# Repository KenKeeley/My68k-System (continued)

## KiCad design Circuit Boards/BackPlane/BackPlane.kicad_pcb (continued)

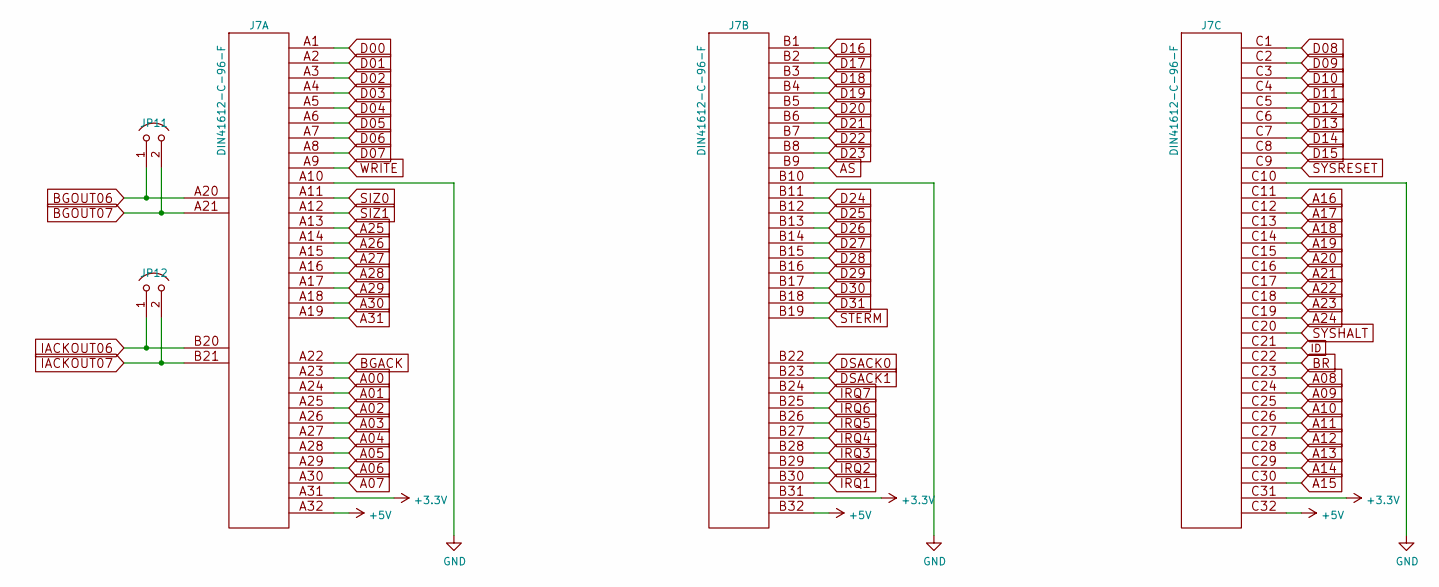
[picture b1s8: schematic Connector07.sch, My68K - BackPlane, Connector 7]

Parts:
J7: DIN41612-C-96-F; Part No. 1656359
JP11, JP12: Jumper; Part No. 1593411

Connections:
+3V3: J7.A31, J7.B31, J7.C31; also elsewhere on the board
+5V: J7.A32, J7.B32, J7.C32; also elsewhere on the board
A00: J7.A23; also elsewhere on the board
A01: J7.A24; also elsewhere on the board
A02: J7.A25; also elsewhere on the board
A03: J7.A26; also elsewhere on the board
A04: J7.A27; also elsewhere on the board
A05: J7.A28; also elsewhere on the board
A06: J7.A29; also elsewhere on the board
A07: J7.A30; also elsewhere on the board
A08: J7.C23; also elsewhere on the board
A09: J7.C24; also elsewhere on the board
A10: J7.C25; also elsewhere on the board
A11: J7.C26; also elsewhere on the board
A12: J7.C27; also elsewhere on the board
A13: J7.C28; also elsewhere on the board
A14: J7.C29; also elsewhere on the board
A15: J7.C30; also elsewhere on the board
A16: J7.C11; also elsewhere on the board
A17: J7.C12; also elsewhere on the board
A18: J7.C13; also elsewhere on the board
A19: J7.C14; also elsewhere on the board
A20: J7.C15; also elsewhere on the board
A21: J7.C16; also elsewhere on the board
A22: J7.C17; also elsewhere on the board
A23: J7.C18; also elsewhere on the board
A24: J7.C19; also elsewhere on the board
A25: J7.A13; also elsewhere on the board
A26: J7.A14; also elsewhere on the board
A27: J7.A15; also elsewhere on the board
A28: J7.A16; also elsewhere on the board
A29: J7.A17; also elsewhere on the board
A30: J7.A18; also elsewhere on the board
A31: J7.A19; also elsewhere on the board
AS: J7.B9; also elsewhere on the board
BGACK: J7.A22; also elsewhere on the board
BGOUT06: J7.A20, JP11.1; also elsewhere on the board
BGOUT07: J7.A21, JP11.2; also elsewhere on the board
BR: J7.C22; also elsewhere on the board
D00: J7.A1; also elsewhere on the board
D01: J7.A2; also elsewhere on the board
D02: J7.A3; also elsewhere on the board
D03: J7.A4; also elsewhere on the board
D04: J7.A5; also elsewhere on the board
D05: J7.A6; also elsewhere on the board
D06: J7.A7; also elsewhere on the board
D07: J7.A8; also elsewhere on the board
D08: J7.C1; also elsewhere on the board
D09: J7.C2; also elsewhere on the board
D10: J7.C3; also elsewhere on the board
D11: J7.C4; also elsewhere on the board
D12: J7.C5; also elsewhere on the board
D13: J7.C6; also elsewhere on the board
D14: J7.C7; also elsewhere on the board
D15: J7.C8; also elsewhere on the board
D16: J7.B1; also elsewhere on the board
D17: J7.B2; also elsewhere on the board
D18: J7.B3; also elsewhere on the board
D19: J7.B4; also elsewhere on the board
D20: J7.B5; also elsewhere on the board
D21: J7.B6; also elsewhere on the board
D22: J7.B7; also elsewhere on the board
D23: J7.B8; also elsewhere on the board
D24: J7.B11; also elsewhere on the board
D25: J7.B12; also elsewhere on the board
D26: J7.B13; also elsewhere on the board
D27: J7.B14; also elsewhere on the board
D28: J7.B15; also elsewhere on the board
D29: J7.B16; also elsewhere on the board
D30: J7.B17; also elsewhere on the board
D31: J7.B18; also elsewhere on the board
DSACK0: J7.B22; also elsewhere on the board
DSACK1: J7.B23; also elsewhere on the board
GND: J7.33 (GND), J7.34 (GND), J7.A10, J7.B10, J7.C10; also elsewhere on the board
IACKOUT06: J7.B20, JP12.1; also elsewhere on the board
IACKOUT07: J7.B21, JP12.2; also elsewhere on the board
ID: J7.C21; also elsewhere on the board
IRQ1: J7.B30; also elsewhere on the board
IRQ2: J7.B29; also elsewhere on the board
IRQ3: J7.B28; also elsewhere on the board
IRQ4: J7.B27; also elsewhere on the board
IRQ5: J7.B26; also elsewhere on the board
IRQ6: J7.B25; also elsewhere on the board
IRQ7: J7.B24; also elsewhere on the board
SIZ0: J7.A11; also elsewhere on the board
SIZ1: J7.A12; also elsewhere on the board
STERM: J7.B19; also elsewhere on the board
SYSHALT: J7.C20; also elsewhere on the board
SYSRESET: J7.C9; also elsewhere on the board
WRITE: J7.A9; also elsewhere on the board

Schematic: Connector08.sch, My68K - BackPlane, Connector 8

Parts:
J8: DIN41612-C-96-F; Part No. 1656359
JP13, JP14: Jumper; Part No. 1593411

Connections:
+3V3: J8.A31, J8.B31, J8.C31; also elsewhere on the board
+5V: J8.A32, J8.B32, J8.C32; also elsewhere on the board
A00: J8.A23; also elsewhere on the board
A01: J8.A24; also elsewhere on the board
A02: J8.A25; also elsewhere on the board
A03: J8.A26; also elsewhere on the board
A04: J8.A27; also elsewhere on the board
A05: J8.A28; also elsewhere on the board
A06: J8.A29; also elsewhere on the board
A07: J8.A30; also elsewhere on the board
A08: J8.C23; also elsewhere on the board
A09: J8.C24; also elsewhere on the board
A10: J8.C25; also elsewhere on the board
A11: J8.C26; also elsewhere on the board
A12: J8.C27; also elsewhere on the board
A13: J8.C28; also elsewhere on the board
A14: J8.C29; also elsewhere on the board
A15: J8.C30; also elsewhere on the board
A16: J8.C11; also elsewhere on the board
A17: J8.C12; also elsewhere on the board
A18: J8.C13; also elsewhere on the board
A19: J8.C14; also elsewhere on the board
A20: J8.C15; also elsewhere on the board
A21: J8.C16; also elsewhere on the board
A22: J8.C17; also elsewhere on the board
A23: J8.C18; also elsewhere on the board
A24: J8.C19; also elsewhere on the board
A25: J8.A13; also elsewhere on the board
A26: J8.A14; also elsewhere on the board
A27: J8.A15; also elsewhere on the board
A28: J8.A16; also elsewhere on the board
A29: J8.A17; also elsewhere on the board
A30: J8.A18; also elsewhere on the board
A31: J8.A19; also elsewhere on the board
AS: J8.B9; also elsewhere on the board
BGACK: J8.A22; also elsewhere on the board
BGOUT07: J8.A20, JP13.1; also elsewhere on the board
BGOUT08: J8.A21, JP13.2; also elsewhere on the board
BR: J8.C22; also elsewhere on the board
D00: J8.A1; also elsewhere on the board
D01: J8.A2; also elsewhere on the board
D02: J8.A3; also elsewhere on the board
D03: J8.A4; also elsewhere on the board
D04: J8.A5; also elsewhere on the board
D05: J8.A6; also elsewhere on the board
D06: J8.A7; also elsewhere on the board
D07: J8.A8; also elsewhere on the board
D08: J8.C1; also elsewhere on the board
D09: J8.C2; also elsewhere on the board
D10: J8.C3; also elsewhere on the board
D11: J8.C4; also elsewhere on the board
D12: J8.C5; also elsewhere on the board
D13: J8.C6; also elsewhere on the board
D14: J8.C7; also elsewhere on the board
D15: J8.C8; also elsewhere on the board
D16: J8.B1; also elsewhere on the board
D17: J8.B2; also elsewhere on the board
D18: J8.B3; also elsewhere on the board
D19: J8.B4; also elsewhere on the board
D20: J8.B5; also elsewhere on the board
D21: J8.B6; also elsewhere on the board
D22: J8.B7; also elsewhere on the board
D23: J8.B8; also elsewhere on the board
D24: J8.B11; also elsewhere on the board
D25: J8.B12; also elsewhere on the board
D26: J8.B13; also elsewhere on the board
D27: J8.B14; also elsewhere on the board
D28: J8.B15; also elsewhere on the board
D29: J8.B16; also elsewhere on the board
D30: J8.B17; also elsewhere on the board
D31: J8.B18; also elsewhere on the board
DSACK0: J8.B22; also elsewhere on the board
DSACK1: J8.B23; also elsewhere on the board
GND: J8.33 (GND), J8.34 (GND), J8.A10, J8.B10, J8.C10; also elsewhere on the board
IACKOUT07: J8.B20, JP14.1; also elsewhere on the board
IACKOUT08: J8.B21, JP14.2; also elsewhere on the board
ID: J8.C21; also elsewhere on the board
IRQ1: J8.B30; also elsewhere on the board
IRQ2: J8.B29; also elsewhere on the board
IRQ3: J8.B28; also elsewhere on the board
IRQ4: J8.B27; also elsewhere on the board
IRQ5: J8.B26; also elsewhere on the board
IRQ6: J8.B25; also elsewhere on the board
IRQ7: J8.B24; also elsewhere on the board
SIZ0: J8.A11; also elsewhere on the board
SIZ1: J8.A12; also elsewhere on the board
STERM: J8.B19; also elsewhere on the board
SYSHALT: J8.C20; also elsewhere on the board
SYSRESET: J8.C9; also elsewhere on the board
WRITE: J8.A9; also elsewhere on the board

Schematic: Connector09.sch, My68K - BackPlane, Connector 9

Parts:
J9: DIN41612-C-96-F; Part No. 1656359
JP15, JP16: Jumper; Part No. 1593411

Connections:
+3V3: J9.A31, J9.B31, J9.C31; also elsewhere on the board
+5V: J9.A32, J9.B32, J9.C32; also elsewhere on the board
A00: J9.A23; also elsewhere on the board
A01: J9.A24; also elsewhere on the board
A02: J9.A25; also elsewhere on the board
A03: J9.A26; also elsewhere on the board
A04: J9.A27; also elsewhere on the board
A05: J9.A28; also elsewhere on the board
A06: J9.A29; also elsewhere on the board
A07: J9.A30; also elsewhere on the board
A08: J9.C23; also elsewhere on the board
A09: J9.C24; also elsewhere on the board
A10: J9.C25; also elsewhere on the board
A11: J9.C26; also elsewhere on the board
A12: J9.C27; also elsewhere on the board
A13: J9.C28; also elsewhere on the board
A14: J9.C29; also elsewhere on the board
A15: J9.C30; also elsewhere on the board
A16: J9.C11; also elsewhere on the board
A17: J9.C12; also elsewhere on the board
A18: J9.C13; also elsewhere on the board
A19: J9.C14; also elsewhere on the board
A20: J9.C15; also elsewhere on the board
A21: J9.C16; also elsewhere on the board
A22: J9.C17; also elsewhere on the board
A23: J9.C18; also elsewhere on the board
A24: J9.C19; also elsewhere on the board
A25: J9.A13; also elsewhere on the board
A26: J9.A14; also elsewhere on the board
A27: J9.A15; also elsewhere on the board
A28: J9.A16; also elsewhere on the board
A29: J9.A17; also elsewhere on the board
A30: J9.A18; also elsewhere on the board
A31: J9.A19; also elsewhere on the board
AS: J9.B9; also elsewhere on the board
BGACK: J9.A22; also elsewhere on the board
BGOUT08: J9.A20, JP15.1; also elsewhere on the board
BGOUT09: J9.A21, JP15.2; also elsewhere on the board
BR: J9.C22; also elsewhere on the board
D00: J9.A1; also elsewhere on the board
D01: J9.A2; also elsewhere on the board
D02: J9.A3; also elsewhere on the board
D03: J9.A4; also elsewhere on the board
D04: J9.A5; also elsewhere on the board
D05: J9.A6; also elsewhere on the board
D06: J9.A7; also elsewhere on the board
D07: J9.A8; also elsewhere on the board
D08: J9.C1; also elsewhere on the board
D09: J9.C2; also elsewhere on the board
D10: J9.C3; also elsewhere on the board
D11: J9.C4; also elsewhere on the board
D12: J9.C5; also elsewhere on the board
D13: J9.C6; also elsewhere on the board
D14: J9.C7; also elsewhere on the board
D15: J9.C8; also elsewhere on the board
D16: J9.B1; also elsewhere on the board
D17: J9.B2; also elsewhere on the board
D18: J9.B3; also elsewhere on the board
D19: J9.B4; also elsewhere on the board
D20: J9.B5; also elsewhere on the board
D21: J9.B6; also elsewhere on the board
D22: J9.B7; also elsewhere on the board
D23: J9.B8; also elsewhere on the board
D24: J9.B11; also elsewhere on the board
D25: J9.B12; also elsewhere on the board
D26: J9.B13; also elsewhere on the board
D27: J9.B14; also elsewhere on the board
D28: J9.B15; also elsewhere on the board
D29: J9.B16; also elsewhere on the board
D30: J9.B17; also elsewhere on the board
D31: J9.B18; also elsewhere on the board
DSACK0: J9.B22; also elsewhere on the board
DSACK1: J9.B23; also elsewhere on the board
GND: J9.33 (GND), J9.34 (GND), J9.A10, J9.B10, J9.C10; also elsewhere on the board
IACKOUT08: J9.B20, JP16.1; also elsewhere on the board
IACKOUT09: J9.B21, JP16.2; also elsewhere on the board
ID: J9.C21; also elsewhere on the board
IRQ1: J9.B30; also elsewhere on the board
IRQ2: J9.B29; also elsewhere on the board
IRQ3: J9.B28; also elsewhere on the board
IRQ4: J9.B27; also elsewhere on the board
IRQ5: J9.B26; also elsewhere on the board
IRQ6: J9.B25; also elsewhere on the board
IRQ7: J9.B24; also elsewhere on the board
SIZ0: J9.A11; also elsewhere on the board
SIZ1: J9.A12; also elsewhere on the board
STERM: J9.B19; also elsewhere on the board
SYSHALT: J9.C20; also elsewhere on the board
SYSRESET: J9.C9; also elsewhere on the board
WRITE: J9.A9; also elsewhere on the board

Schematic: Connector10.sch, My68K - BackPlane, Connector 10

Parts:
J10: DIN41612-C-96-F; Part No. 1656359
JP17, JP18: Jumper; Part No. 1593411

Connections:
+3V3: J10.A31, J10.B31, J10.C31; also elsewhere on the board
+5V: J10.A32, J10.B32, J10.C32; also elsewhere on the board
A00: J10.A23; also elsewhere on the board
A01: J10.A24; also elsewhere on the board
A02: J10.A25; also elsewhere on the board
A03: J10.A26; also elsewhere on the board
A04: J10.A27; also elsewhere on the board
A05: J10.A28; also elsewhere on the board
A06: J10.A29; also elsewhere on the board
A07: J10.A30; also elsewhere on the board
A08: J10.C23; also elsewhere on the board
A09: J10.C24; also elsewhere on the board
A10: J10.C25; also elsewhere on the board
A11: J10.C26; also elsewhere on the board
A12: J10.C27; also elsewhere on the board
A13: J10.C28; also elsewhere on the board
A14: J10.C29; also elsewhere on the board
A15: J10.C30; also elsewhere on the board
A16: J10.C11; also elsewhere on the board
A17: J10.C12; also elsewhere on the board
A18: J10.C13; also elsewhere on the board
A19: J10.C14; also elsewhere on the board
A20: J10.C15; also elsewhere on the board
A21: J10.C16; also elsewhere on the board
A22: J10.C17; also elsewhere on the board
A23: J10.C18; also elsewhere on the board
A24: J10.C19; also elsewhere on the board
A25: J10.A13; also elsewhere on the board
A26: J10.A14; also elsewhere on the board
A27: J10.A15; also elsewhere on the board
A28: J10.A16; also elsewhere on the board
A29: J10.A17; also elsewhere on the board
A30: J10.A18; also elsewhere on the board
A31: J10.A19; also elsewhere on the board
AS: J10.B9; also elsewhere on the board
BGACK: J10.A22; also elsewhere on the board
BGOUT09: J10.A20, JP17.1; also elsewhere on the board
BGOUT10: J10.A21, JP17.2; also elsewhere on the board
BR: J10.C22; also elsewhere on the board
D00: J10.A1; also elsewhere on the board
D01: J10.A2; also elsewhere on the board
D02: J10.A3; also elsewhere on the board
D03: J10.A4; also elsewhere on the board
D04: J10.A5; also elsewhere on the board
D05: J10.A6; also elsewhere on the board
D06: J10.A7; also elsewhere on the board
D07: J10.A8; also elsewhere on the board
D08: J10.C1; also elsewhere on the board
D09: J10.C2; also elsewhere on the board
D10: J10.C3; also elsewhere on the board
D11: J10.C4; also elsewhere on the board
D12: J10.C5; also elsewhere on the board
D13: J10.C6; also elsewhere on the board
D14: J10.C7; also elsewhere on the board
D15: J10.C8; also elsewhere on the board
D16: J10.B1; also elsewhere on the board
D17: J10.B2; also elsewhere on the board
D18: J10.B3; also elsewhere on the board
D19: J10.B4; also elsewhere on the board
D20: J10.B5; also elsewhere on the board
D21: J10.B6; also elsewhere on the board
D22: J10.B7; also elsewhere on the board
D23: J10.B8; also elsewhere on the board
D24: J10.B11; also elsewhere on the board
D25: J10.B12; also elsewhere on the board
D26: J10.B13; also elsewhere on the board
D27: J10.B14; also elsewhere on the board
D28: J10.B15; also elsewhere on the board
D29: J10.B16; also elsewhere on the board
D30: J10.B17; also elsewhere on the board
D31: J10.B18; also elsewhere on the board
DSACK0: J10.B22; also elsewhere on the board
DSACK1: J10.B23; also elsewhere on the board
GND: J10.33 (GND), J10.34 (GND), J10.A10, J10.B10, J10.C10; also elsewhere on the board
IACKOUT09: J10.B20, JP18.1; also elsewhere on the board
IACKOUT10: J10.B21, JP18.2; also elsewhere on the board
ID: J10.C21; also elsewhere on the board
IRQ1: J10.B30; also elsewhere on the board
IRQ2: J10.B29; also elsewhere on the board
IRQ3: J10.B28; also elsewhere on the board
IRQ4: J10.B27; also elsewhere on the board
IRQ5: J10.B26; also elsewhere on the board
IRQ6: J10.B25; also elsewhere on the board
IRQ7: J10.B24; also elsewhere on the board
SIZ0: J10.A11; also elsewhere on the board
SIZ1: J10.A12; also elsewhere on the board
STERM: J10.B19; also elsewhere on the board
SYSHALT: J10.C20; also elsewhere on the board
SYSRESET: J10.C9; also elsewhere on the board
WRITE: J10.A9; also elsewhere on the board

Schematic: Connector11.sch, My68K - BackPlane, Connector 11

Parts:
J11: DIN41612-C-96-F; Part No. 1656359
JP19, JP20: Jumper; Part No. 1593411

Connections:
+3V3: J11.A31, J11.B31, J11.C31; also elsewhere on the board
+5V: J11.A32, J11.B32, J11.C32; also elsewhere on the board
A00: J11.A23; also elsewhere on the board
A01: J11.A24; also elsewhere on the board
A02: J11.A25; also elsewhere on the board
A03: J11.A26; also elsewhere on the board
A04: J11.A27; also elsewhere on the board
A05: J11.A28; also elsewhere on the board
A06: J11.A29; also elsewhere on the board
A07: J11.A30; also elsewhere on the board
A08: J11.C23; also elsewhere on the board
A09: J11.C24; also elsewhere on the board
A10: J11.C25; also elsewhere on the board
A11: J11.C26; also elsewhere on the board
A12: J11.C27; also elsewhere on the board
A13: J11.C28; also elsewhere on the board
A14: J11.C29; also elsewhere on the board
A15: J11.C30; also elsewhere on the board
A16: J11.C11; also elsewhere on the board
A17: J11.C12; also elsewhere on the board
A18: J11.C13; also elsewhere on the board
A19: J11.C14; also elsewhere on the board
A20: J11.C15; also elsewhere on the board
A21: J11.C16; also elsewhere on the board
A22: J11.C17; also elsewhere on the board
A23: J11.C18; also elsewhere on the board
A24: J11.C19; also elsewhere on the board
A25: J11.A13; also elsewhere on the board
A26: J11.A14; also elsewhere on the board
A27: J11.A15; also elsewhere on the board
A28: J11.A16; also elsewhere on the board
A29: J11.A17; also elsewhere on the board
A30: J11.A18; also elsewhere on the board
A31: J11.A19; also elsewhere on the board
AS: J11.B9; also elsewhere on the board
BGACK: J11.A22; also elsewhere on the board
BGOUT10: J11.A20, JP19.1; also elsewhere on the board
BGOUT11: J11.A21, JP19.2; also elsewhere on the board
BR: J11.C22; also elsewhere on the board
D00: J11.A1; also elsewhere on the board
D01: J11.A2; also elsewhere on the board
D02: J11.A3; also elsewhere on the board
D03: J11.A4; also elsewhere on the board
D04: J11.A5; also elsewhere on the board
D05: J11.A6; also elsewhere on the board
D06: J11.A7; also elsewhere on the board
D07: J11.A8; also elsewhere on the board
D08: J11.C1; also elsewhere on the board
D09: J11.C2; also elsewhere on the board
D10: J11.C3; also elsewhere on the board
D11: J11.C4; also elsewhere on the board
D12: J11.C5; also elsewhere on the board
D13: J11.C6; also elsewhere on the board
D14: J11.C7; also elsewhere on the board
D15: J11.C8; also elsewhere on the board
D16: J11.B1; also elsewhere on the board
D17: J11.B2; also elsewhere on the board
D18: J11.B3; also elsewhere on the board
D19: J11.B4; also elsewhere on the board
D20: J11.B5; also elsewhere on the board
D21: J11.B6; also elsewhere on the board
D22: J11.B7; also elsewhere on the board
D23: J11.B8; also elsewhere on the board
D24: J11.B11; also elsewhere on the board
D25: J11.B12; also elsewhere on the board
D26: J11.B13; also elsewhere on the board
D27: J11.B14; also elsewhere on the board
D28: J11.B15; also elsewhere on the board
D29: J11.B16; also elsewhere on the board
D30: J11.B17; also elsewhere on the board
D31: J11.B18; also elsewhere on the board
DSACK0: J11.B22; also elsewhere on the board
DSACK1: J11.B23; also elsewhere on the board
GND: J11.33 (GND), J11.34 (GND), J11.A10, J11.B10, J11.C10; also elsewhere on the board
IACKOUT10: J11.B20, JP20.1; also elsewhere on the board
IACKOUT11: J11.B21, JP20.2; also elsewhere on the board
ID: J11.C21; also elsewhere on the board
IRQ1: J11.B30; also elsewhere on the board
IRQ2: J11.B29; also elsewhere on the board
IRQ3: J11.B28; also elsewhere on the board
IRQ4: J11.B27; also elsewhere on the board
IRQ5: J11.B26; also elsewhere on the board
IRQ6: J11.B25; also elsewhere on the board
IRQ7: J11.B24; also elsewhere on the board
SIZ0: J11.A11; also elsewhere on the board
SIZ1: J11.A12; also elsewhere on the board
STERM: J11.B19; also elsewhere on the board
SYSHALT: J11.C20; also elsewhere on the board
SYSRESET: J11.C9; also elsewhere on the board
WRITE: J11.A9; also elsewhere on the board

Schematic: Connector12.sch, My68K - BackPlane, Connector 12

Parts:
J12: DIN41612-C-96-F; Part No. 1656359
JP21, JP22: Jumper; Part No. 1593411

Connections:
+3V3: J12.A31, J12.B31, J12.C31; also elsewhere on the board
+5V: J12.A32, J12.B32, J12.C32; also elsewhere on the board
A00: J12.A23; also elsewhere on the board
A01: J12.A24; also elsewhere on the board
A02: J12.A25; also elsewhere on the board
A03: J12.A26; also elsewhere on the board
A04: J12.A27; also elsewhere on the board
A05: J12.A28; also elsewhere on the board
A06: J12.A29; also elsewhere on the board
A07: J12.A30; also elsewhere on the board
A08: J12.C23; also elsewhere on the board
A09: J12.C24; also elsewhere on the board
A10: J12.C25; also elsewhere on the board
A11: J12.C26; also elsewhere on the board
A12: J12.C27; also elsewhere on the board
A13: J12.C28; also elsewhere on the board
A14: J12.C29; also elsewhere on the board
A15: J12.C30; also elsewhere on the board
A16: J12.C11; also elsewhere on the board
A17: J12.C12; also elsewhere on the board
A18: J12.C13; also elsewhere on the board
A19: J12.C14; also elsewhere on the board
A20: J12.C15; also elsewhere on the board
A21: J12.C16; also elsewhere on the board
A22: J12.C17; also elsewhere on the board
A23: J12.C18; also elsewhere on the board
A24: J12.C19; also elsewhere on the board
A25: J12.A13; also elsewhere on the board
A26: J12.A14; also elsewhere on the board
A27: J12.A15; also elsewhere on the board
A28: J12.A16; also elsewhere on the board
A29: J12.A17; also elsewhere on the board
A30: J12.A18; also elsewhere on the board
A31: J12.A19; also elsewhere on the board
AS: J12.B9; also elsewhere on the board
BGACK: J12.A22; also elsewhere on the board
BGOUT11: J12.A20, JP21.1; also elsewhere on the board
BGOUT12: J12.A21, JP21.2; also elsewhere on the board
BR: J12.C22; also elsewhere on the board
D00: J12.A1; also elsewhere on the board
D01: J12.A2; also elsewhere on the board
D02: J12.A3; also elsewhere on the board
D03: J12.A4; also elsewhere on the board
D04: J12.A5; also elsewhere on the board
D05: J12.A6; also elsewhere on the board
D06: J12.A7; also elsewhere on the board
D07: J12.A8; also elsewhere on the board
D08: J12.C1; also elsewhere on the board
D09: J12.C2; also elsewhere on the board
D10: J12.C3; also elsewhere on the board
D11: J12.C4; also elsewhere on the board
D12: J12.C5; also elsewhere on the board
D13: J12.C6; also elsewhere on the board
D14: J12.C7; also elsewhere on the board
D15: J12.C8; also elsewhere on the board
D16: J12.B1; also elsewhere on the board
D17: J12.B2; also elsewhere on the board
D18: J12.B3; also elsewhere on the board
D19: J12.B4; also elsewhere on the board
D20: J12.B5; also elsewhere on the board
D21: J12.B6; also elsewhere on the board
D22: J12.B7; also elsewhere on the board
D23: J12.B8; also elsewhere on the board
D24: J12.B11; also elsewhere on the board
D25: J12.B12; also elsewhere on the board
D26: J12.B13; also elsewhere on the board
D27: J12.B14; also elsewhere on the board
D28: J12.B15; also elsewhere on the board
D29: J12.B16; also elsewhere on the board
D30: J12.B17; also elsewhere on the board
D31: J12.B18; also elsewhere on the board
DSACK0: J12.B22; also elsewhere on the board
DSACK1: J12.B23; also elsewhere on the board
GND: J12.33 (GND), J12.34 (GND), J12.A10, J12.B10, J12.C10; also elsewhere on the board
IACKOUT11: J12.B20, JP22.1; also elsewhere on the board
IACKOUT12: J12.B21, JP22.2; also elsewhere on the board
ID: J12.C21; also elsewhere on the board
IRQ1: J12.B30; also elsewhere on the board
IRQ2: J12.B29; also elsewhere on the board
IRQ3: J12.B28; also elsewhere on the board
IRQ4: J12.B27; also elsewhere on the board
IRQ5: J12.B26; also elsewhere on the board
IRQ6: J12.B25; also elsewhere on the board
IRQ7: J12.B24; also elsewhere on the board
SIZ0: J12.A11; also elsewhere on the board
SIZ1: J12.A12; also elsewhere on the board
STERM: J12.B19; also elsewhere on the board
SYSHALT: J12.C20; also elsewhere on the board
SYSRESET: J12.C9; also elsewhere on the board
WRITE: J12.A9; also elsewhere on the board

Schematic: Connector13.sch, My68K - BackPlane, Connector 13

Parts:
J13: DIN41612-C-96-F; Part No. 1656359
JP23, JP24: Jumper; Part No. 1593411

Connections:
+3V3: J13.A31, J13.B31, J13.C31; also elsewhere on the board
+5V: J13.A32, J13.B32, J13.C32; also elsewhere on the board
A00: J13.A23; also elsewhere on the board
A01: J13.A24; also elsewhere on the board
A02: J13.A25; also elsewhere on the board
A03: J13.A26; also elsewhere on the board
A04: J13.A27; also elsewhere on the board
A05: J13.A28; also elsewhere on the board
A06: J13.A29; also elsewhere on the board
A07: J13.A30; also elsewhere on the board
A08: J13.C23; also elsewhere on the board
A09: J13.C24; also elsewhere on the board
A10: J13.C25; also elsewhere on the board
A11: J13.C26; also elsewhere on the board
A12: J13.C27; also elsewhere on the board
A13: J13.C28; also elsewhere on the board
A14: J13.C29; also elsewhere on the board
A15: J13.C30; also elsewhere on the board
A16: J13.C11; also elsewhere on the board
A17: J13.C12; also elsewhere on the board
A18: J13.C13; also elsewhere on the board
A19: J13.C14; also elsewhere on the board
A20: J13.C15; also elsewhere on the board
A21: J13.C16; also elsewhere on the board
A22: J13.C17; also elsewhere on the board
A23: J13.C18; also elsewhere on the board
A24: J13.C19; also elsewhere on the board
A25: J13.A13; also elsewhere on the board
A26: J13.A14; also elsewhere on the board
A27: J13.A15; also elsewhere on the board
A28: J13.A16; also elsewhere on the board
A29: J13.A17; also elsewhere on the board
A30: J13.A18; also elsewhere on the board
A31: J13.A19; also elsewhere on the board
AS: J13.B9; also elsewhere on the board
BGACK: J13.A22; also elsewhere on the board
BGOUT12: J13.A20, JP23.1; also elsewhere on the board
BGOUT13: J13.A21, JP23.2; also elsewhere on the board
BR: J13.C22; also elsewhere on the board
D00: J13.A1; also elsewhere on the board
D01: J13.A2; also elsewhere on the board
D02: J13.A3; also elsewhere on the board
D03: J13.A4; also elsewhere on the board
D04: J13.A5; also elsewhere on the board
D05: J13.A6; also elsewhere on the board
D06: J13.A7; also elsewhere on the board
D07: J13.A8; also elsewhere on the board
D08: J13.C1; also elsewhere on the board
D09: J13.C2; also elsewhere on the board
D10: J13.C3; also elsewhere on the board
D11: J13.C4; also elsewhere on the board
D12: J13.C5; also elsewhere on the board
D13: J13.C6; also elsewhere on the board
D14: J13.C7; also elsewhere on the board
D15: J13.C8; also elsewhere on the board
D16: J13.B1; also elsewhere on the board
D17: J13.B2; also elsewhere on the board
D18: J13.B3; also elsewhere on the board
D19: J13.B4; also elsewhere on the board
D20: J13.B5; also elsewhere on the board
D21: J13.B6; also elsewhere on the board
D22: J13.B7; also elsewhere on the board
D23: J13.B8; also elsewhere on the board
D24: J13.B11; also elsewhere on the board
D25: J13.B12; also elsewhere on the board
D26: J13.B13; also elsewhere on the board
D27: J13.B14; also elsewhere on the board
D28: J13.B15; also elsewhere on the board
D29: J13.B16; also elsewhere on the board
D30: J13.B17; also elsewhere on the board
D31: J13.B18; also elsewhere on the board
DSACK0: J13.B22; also elsewhere on the board
DSACK1: J13.B23; also elsewhere on the board
GND: J13.33 (GND), J13.34 (GND), J13.A10, J13.B10, J13.C10; also elsewhere on the board
IACKOUT12: J13.B20, JP24.1; also elsewhere on the board
IACKOUT13: J13.B21, JP24.2; also elsewhere on the board
ID: J13.C21; also elsewhere on the board
IRQ1: J13.B30; also elsewhere on the board
IRQ2: J13.B29; also elsewhere on the board
IRQ3: J13.B28; also elsewhere on the board
IRQ4: J13.B27; also elsewhere on the board
IRQ5: J13.B26; also elsewhere on the board
IRQ6: J13.B25; also elsewhere on the board
IRQ7: J13.B24; also elsewhere on the board
SIZ0: J13.A11; also elsewhere on the board
SIZ1: J13.A12; also elsewhere on the board
STERM: J13.B19; also elsewhere on the board
SYSHALT: J13.C20; also elsewhere on the board
SYSRESET: J13.C9; also elsewhere on the board
WRITE: J13.A9; also elsewhere on the board

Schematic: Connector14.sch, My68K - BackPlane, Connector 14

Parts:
J14: DIN41612-C-96-F; Part No. 1656359
JP25, JP26: Jumper; Part No. 1593411

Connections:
+3V3: J14.A31, J14.B31, J14.C31; also elsewhere on the board
+5V: J14.A32, J14.B32, J14.C32; also elsewhere on the board
A00: J14.A23; also elsewhere on the board
A01: J14.A24; also elsewhere on the board
A02: J14.A25; also elsewhere on the board
A03: J14.A26; also elsewhere on the board
A04: J14.A27; also elsewhere on the board
A05: J14.A28; also elsewhere on the board
A06: J14.A29; also elsewhere on the board
A07: J14.A30; also elsewhere on the board
A08: J14.C23; also elsewhere on the board
A09: J14.C24; also elsewhere on the board
A10: J14.C25; also elsewhere on the board
A11: J14.C26; also elsewhere on the board
A12: J14.C27; also elsewhere on the board
A13: J14.C28; also elsewhere on the board
A14: J14.C29; also elsewhere on the board
A15: J14.C30; also elsewhere on the board
A16: J14.C11; also elsewhere on the board
A17: J14.C12; also elsewhere on the board
A18: J14.C13; also elsewhere on the board
A19: J14.C14; also elsewhere on the board
A20: J14.C15; also elsewhere on the board
A21: J14.C16; also elsewhere on the board
A22: J14.C17; also elsewhere on the board
A23: J14.C18; also elsewhere on the board
A24: J14.C19; also elsewhere on the board
A25: J14.A13; also elsewhere on the board
A26: J14.A14; also elsewhere on the board
A27: J14.A15; also elsewhere on the board
A28: J14.A16; also elsewhere on the board
A29: J14.A17; also elsewhere on the board
A30: J14.A18; also elsewhere on the board
A31: J14.A19; also elsewhere on the board
AS: J14.B9; also elsewhere on the board
BGACK: J14.A22; also elsewhere on the board
BGOUT13: J14.A20, JP25.1; also elsewhere on the board
BGOUT14: J14.A21, JP25.2; also elsewhere on the board
BR: J14.C22; also elsewhere on the board
D00: J14.A1; also elsewhere on the board
D01: J14.A2; also elsewhere on the board
D02: J14.A3; also elsewhere on the board
D03: J14.A4; also elsewhere on the board
D04: J14.A5; also elsewhere on the board
D05: J14.A6; also elsewhere on the board
D06: J14.A7; also elsewhere on the board
D07: J14.A8; also elsewhere on the board
D08: J14.C1; also elsewhere on the board
D09: J14.C2; also elsewhere on the board
D10: J14.C3; also elsewhere on the board
D11: J14.C4; also elsewhere on the board
D12: J14.C5; also elsewhere on the board
D13: J14.C6; also elsewhere on the board
D14: J14.C7; also elsewhere on the board
D15: J14.C8; also elsewhere on the board
D16: J14.B1; also elsewhere on the board
D17: J14.B2; also elsewhere on the board
D18: J14.B3; also elsewhere on the board
D19: J14.B4; also elsewhere on the board
D20: J14.B5; also elsewhere on the board
D21: J14.B6; also elsewhere on the board
D22: J14.B7; also elsewhere on the board
D23: J14.B8; also elsewhere on the board
D24: J14.B11; also elsewhere on the board
D25: J14.B12; also elsewhere on the board
D26: J14.B13; also elsewhere on the board
D27: J14.B14; also elsewhere on the board
D28: J14.B15; also elsewhere on the board
D29: J14.B16; also elsewhere on the board
D30: J14.B17; also elsewhere on the board
D31: J14.B18; also elsewhere on the board
DSACK0: J14.B22; also elsewhere on the board
DSACK1: J14.B23; also elsewhere on the board
GND: J14.33 (GND), J14.34 (GND), J14.A10, J14.B10, J14.C10; also elsewhere on the board
IACKOUT13: J14.B20, JP26.1; also elsewhere on the board
IACKOUT14: J14.B21, JP26.2; also elsewhere on the board
ID: J14.C21; also elsewhere on the board
IRQ1: J14.B30; also elsewhere on the board
IRQ2: J14.B29; also elsewhere on the board
IRQ3: J14.B28; also elsewhere on the board
IRQ4: J14.B27; also elsewhere on the board
IRQ5: J14.B26; also elsewhere on the board
IRQ6: J14.B25; also elsewhere on the board
IRQ7: J14.B24; also elsewhere on the board
SIZ0: J14.A11; also elsewhere on the board
SIZ1: J14.A12; also elsewhere on the board
STERM: J14.B19; also elsewhere on the board
SYSHALT: J14.C20; also elsewhere on the board
SYSRESET: J14.C9; also elsewhere on the board
WRITE: J14.A9; also elsewhere on the board
